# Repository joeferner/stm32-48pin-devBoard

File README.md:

# STM32 48pin Development Board

Supports the STM32F103CBT6 and many other STM32 48pin chips. Breaks out the USB, all pins, and JTAG.

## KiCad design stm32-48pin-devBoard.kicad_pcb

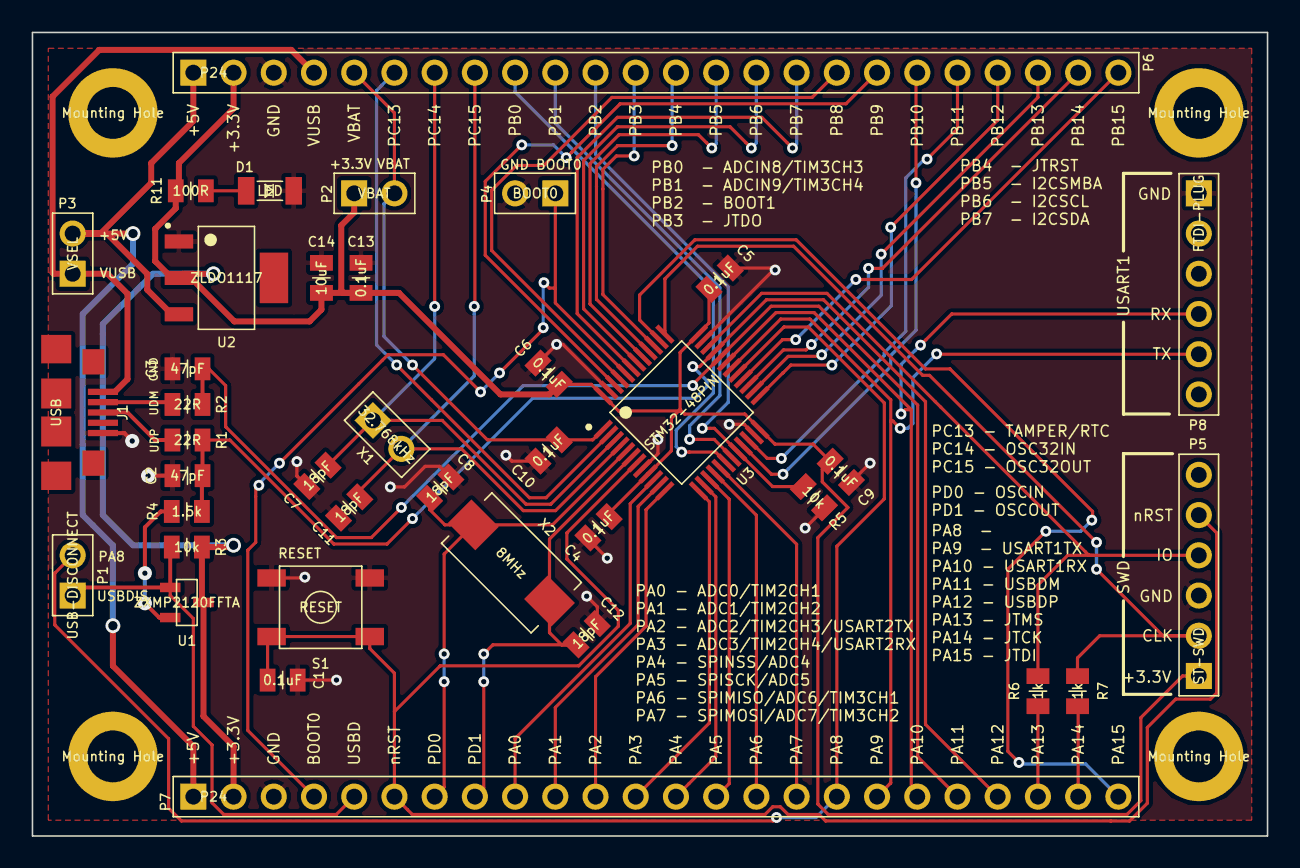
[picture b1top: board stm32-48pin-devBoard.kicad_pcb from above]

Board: 2 copper layers, 78.0 x 50.7 mm, 42 parts (0 on the bottom side), 51 nets.

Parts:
C1, C4, C5, C6, C9, C10, C13: 0.1uF; CAPC2012X100N
C2, C3: 47pF; CAPC2012X100N
C7, C8, C11, C12: 18pF; CAPC2012X100N
C14: 10uF; CAPC2012X100N
D1: LED; LEDC3216X100N
J1: USB; JST_UB-MC5BR3-SD204-4S-NMP
M1, M2, M3, M4: Mounting Hole; MTGNP565H328Z565P
P1: USB-DISCONNECT; HDRV2W66P254_1X2_508X249X838P
P2: VBAT; HDRV2W66P254_1X2_508X249X838P
P3: VSEL; HDRV2W66P254_1X2_508X249X838P
P4: BOOT0; HDRV2W66P254_1X2_508X249X838P
P5: ST-SWD; HDRV6W66P254_1X6_1524X249X838P
P6, P7: P24; HDRV24W66P254_1X24_6096X249X838P
P8: FTDI-PLUG; HDRV6W66P254_1X6_1524X249X838P
R1, R2: 22R; RESC2012X100N
R3, R5: 10k; RESC2012X100N
R4: 1.5k; RESC2012X100N
R6, R7: 1k; RESC2012X100N
R11: 100R; RESC2012X100N
S1: RESET; CKCOMP-PTS525SM10SMTR
U1: ZXMP2120FFTA; SOT95P237X112_123-3N
U2: ZLDO1117; SOT230P700X180-4N
U3: STM32-48PIN; QFP50P900X900X160-48N
X1: 32.768kHz; HDRV2W66P254_1X2_508X249X838P
X2: 8MHz; XTAL8045X200N

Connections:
+3.3V: C4.1, C5.1, C6.1, C9.1, C13.1, C14.1, P2.1, P5.1, P6.2, P7.2, R3.2, R11.2, U1.3, U2.2, U3.9, U3.24, U3.36, U3.48
+5V: P3.2, P6.1, P7.1, U2.3
/BOOT0: P4.1, P7.4, U3.44
/PA0: P7.9, U3.10
/PA1: P7.10, U3.11
/PA2: P7.11, U3.12
/PA3: P7.12, U3.13
/PA4: P7.13, U3.14
/PA5: P7.14, U3.15
/PA6: P7.15, U3.16
/PA7: P7.16, U3.17
/PA8: P1.2, P7.17, U3.29
/PA9: P7.18, P8.5, U3.30
/PA10: P7.19, P8.4, U3.31
/PA11: C3.1, P7.20, R2.2, U3.32
/PA12: C2.1, P7.21, R1.2, R4.1, U3.33
/PA13: P7.22, R6.1
/PA14: P7.23, R7.1
/PA15: P7.24, U3.38
/PB0: P6.9, U3.18
/PB1: P6.10, U3.19
/PB2: P6.11, R5.1, U3.20
/PB3: P6.12, U3.39
/PB4: P6.13, U3.40
/PB5: P6.14, U3.41
/PB6: P6.15, U3.42
/PB7: P6.16, U3.43
/PB8: P6.17, U3.45
/PB9: P6.18, U3.46
/PB10: P6.19, U3.21
/PB11: P6.20, U3.22
/PB12: P6.21, U3.25
/PB13: P6.22, U3.26
/PB14: P6.23, U3.27
/PB15: P6.24, U3.28
/PC13: P6.6, U3.2
/PC14: C7.1, P6.7, U3.3, X1.1
/PC15: C11.1, P6.8, U3.4, X1.2
/PD0: C8.1, P7.7, U3.5, X2.2
/PD1: C12.1, P7.8, U3.6, X2.1
/SWCLK: P5.2, R7.2, U3.37
/SWDIO: P5.4, R6.2, U3.34
/USB-DISCONNECT: P1.1, P7.5, R3.1, U1.1
/USBDM: J1.2, R2.1
/USBDP: J1.3, R1.1
/VBAT: C10.1, P2.2, P6.5, U3.1
/VUSB: J1.1, P3.1, P6.4
/nRST: C1.1, P5.5, P7.6, S1.3, S1.4, U3.7
GND: C1.2, C2.2, C3.2, C4.2, C5.2, C6.2, C7.2, C8.2, C9.2, C10.2, C11.2, C12.2, C13.2, C14.2, D1.2, J1.5, P4.2, P5.3, P6.3, P7.3, P8.1, R5.2, S1.1, S1.2, U2.1, U3.8, U3.23, U3.35, U3.47
unnamed: D1.1, R11.1
unnamed: R4.2, U1.2

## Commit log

2013-10-23 initial
2013-10-23 added kicad-library substree
2013-10-23 moved libs
2013-10-23 initial lists
2013-10-23 more updates
2013-10-23 schematic updates
2013-10-23 more schematic work
2013-10-23 format
2013-10-23 update kicad library
2013-10-24 added power flags to schematic
2013-10-24 update from kicad
2013-10-24 working on association
2013-10-24 added 1x24 header
2013-10-24 update USB to longer leads
2013-10-24 finished pcb
2013-10-25 added github label to pcb
2013-10-25 readme
2013-10-25 version 2013-10-24
2013-11-13 initial test firmware
2013-11-13 change xtal to 32.768
2013-11-13 more build
2013-11-13 working?
2013-11-13 working
2013-12-11 update pcb
2013-12-11 save to kicad library
2013-12-11 add MOSFET-P
2014-08-13 upgrade to new kicad mod layout
2014-08-13 more sitching to new kicad mod layout
2014-08-13 more upgrade
2014-08-13 remove kicad-library as subtree
2014-08-15 switch to new kicad mod format and started rework
2014-08-17 re-route based on new issues
2014-08-22 add pdf from 2013-10-24 and fixed directory name
